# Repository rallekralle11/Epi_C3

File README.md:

# Epi_C3
 Maybe the smallest ESP32 board with USB-C and onboard antenna.
 
 For sale now!

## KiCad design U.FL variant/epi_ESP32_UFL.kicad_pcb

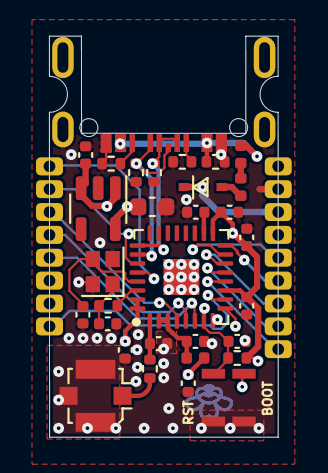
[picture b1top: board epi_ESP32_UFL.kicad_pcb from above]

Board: 4 copper layers, 12.7 x 22.3 mm, 36 parts (0 on the bottom side), 31 nets.

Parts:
C1, C2, C5, C7: 100nF; C_0402_1005Metric
C3, C4, C6: TBD; C_0402_1005Metric
C8, C9, C11, C12, C13: 1µF; C_0402_1005Metric
C10: 22µF; C_0603_1608Metric
D1: D; SOD323_bättre (2022_12_20 17_46_41 UTC)
DRILL1, DRILL2: NPTH
F1: 500mA; Fuse_0402_1005Metric
FB1, FB2: Ferrite; L_0402_1005Metric
J1: Conn_01x08; PinHeader_1x08_P1.27mm_Vertical
J2: Conn_01x09; PinSocket_1x09_P1.27mm_Vertical
J3: USB_C_Receptacle_USB2.0; USB-C MC-314C-4P16_V2 (2023_01_13 17_48_46 UTC)
J4: Conn_Coaxial_Small; U.FL_Molex_MCRF_73412-0110_Vertical
L1: TBD; R_0402_1005Metric
R2: 22Ω; R_0402_1005Metric
R4, R5: 5,1kΩ; R_0402_1005Metric
R6: 10kΩ; R_0402_1005Metric
RV1, RV2, RV3: Varistor; R_0402_1005Metric
SW1, SW2: SW_MEC_5G; R-668048
U1: ESP32-C3; QFN-32-1EP_5x5mm_P0.5mm_EP3.45x3.45mm
U2: RT9080; SOT-23-5
Y1: Crystal; Crystal_SMD_2016-4Pin_2.0x1.6mm

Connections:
+3.3V: C1.2, C2.2, C7.2, C8.2, C10.2, C13.2, FB2.1, J2.1, R6.1, U1.11 (VDD3P3_RTC), U1.17 (VDD3P3_CPU), U1.31 (VDDA), U1.32 (VDDA), U2.5 (OUT)
+5V: FB1.1, J3.A4 (VBUS), J3.A9 (VBUS), RV1.1
BOOT: J2.5, SW1.1 (A), U1.15 (GPIO9/BOOT)
D+: J3.A6 (D+), J3.B6 (D+), RV2.2, U1.26 (GPIO19/USB_D+)
D-: J3.A7 (D-), J3.B7 (D-), RV3.2, U1.25 (GPIO18/USB_D-)
EN: C11.2, J2.4, R6.2, SW2.1 (A), U1.7 (CHIP_EN)
GND: C1.1, C2.1, C3.1, C4.1, C5.1, C6.1, C7.1, C8.1, C9.1, C10.1, C11.1, C12.2, C13.1, J2.2, J3.A1 (GND), J3.B12 (GND), J3.S1 (SHIELD), J4.2 (Ext), R4.2, R5.2, RV1.2, RV2.1, RV3.1, SW1.3 (B), SW2.3 (B), U1.33 (GND), U2.2 (GND), Y1.2, Y1.4
IO0: J1.3, U1.4 (XTAL_32K_P/ADC1_CH0)
IO1: J1.4, U1.5 (XTAL_32K_N/ADC1_CH1)
IO2: J1.5, U1.6 (GPIO2/ADC1_CH2)
IO3: J1.6, U1.8 (GPIO3/ADC1_CH3)
IO4: J1.7, U1.9 (MTMS/GPIO4/ADC1_CH4)
IO5: J1.8, U1.10 (MTDI/GPIO5/ADC2_CH0)
IO6: J2.9, U1.12 (MTCK/GPIO6)
IO7: J2.8, U1.13 (MTDO/GPIO7)
IO8: J2.7, U1.14 (GPIO8)
IO10: J2.6, U1.16 (GPIO10)
unnamed: C4.2, R2.1, Y1.1
unnamed: C5.2, FB2.2, U1.2 (VDD3P3), U1.3 (VDD3P3)
unnamed: D1.2 (A), F1.2
unnamed: F1.1, FB1.2
unnamed: J3.A5 (CC1), R5.1
unnamed: J3.B5 (CC2), R4.1
unnamed: J4.1 (In), L1.2
unnamed: C6.2, L1.1, U1.1 (LNA_IN)
unnamed: C12.1, U1.18 (VDD_SPI/GPIO11)
unnamed: C3.2, U1.29 (XTAL_N), Y1.3
unnamed: R2.2, U1.30 (XTAL_P)
U0RXD: J1.2, U1.27 (U0RXD/GPIO20)
U0TXD: J1.1, U1.28 (U0TXD/GPIO21)
VCC: C9.2, D1.1 (K), J2.3, U2.1 (IN), U2.3 (EN)

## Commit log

2024-04-02 init
2024-08-14 pictures and schematic
2024-08-14 pinout document
2024-08-16 new revision
2024-08-16 new gerbers
2024-08-19 pictures
2024-08-20 new BOM
2024-09-04 added U.FL variant
2024-09-13 forgot the licence + more
